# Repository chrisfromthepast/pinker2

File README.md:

# pinker2
 Phantom Powered Pink noise generator

Plug it into a +48V Phantom Powered mic preamp to create pink noise.

Thia project is still in development, and owes EVERYTHING to this thread:
https://groupdiy.com/threads/will-this-48-v-pink-noise-source-work.85625/page-4#post-1117816

A reverse biased BJT provides noise, a op amp gain stage comes next, followed by an op amp filter stage, which does its best to turn white noise into pink noise. the output is impedance balanced.

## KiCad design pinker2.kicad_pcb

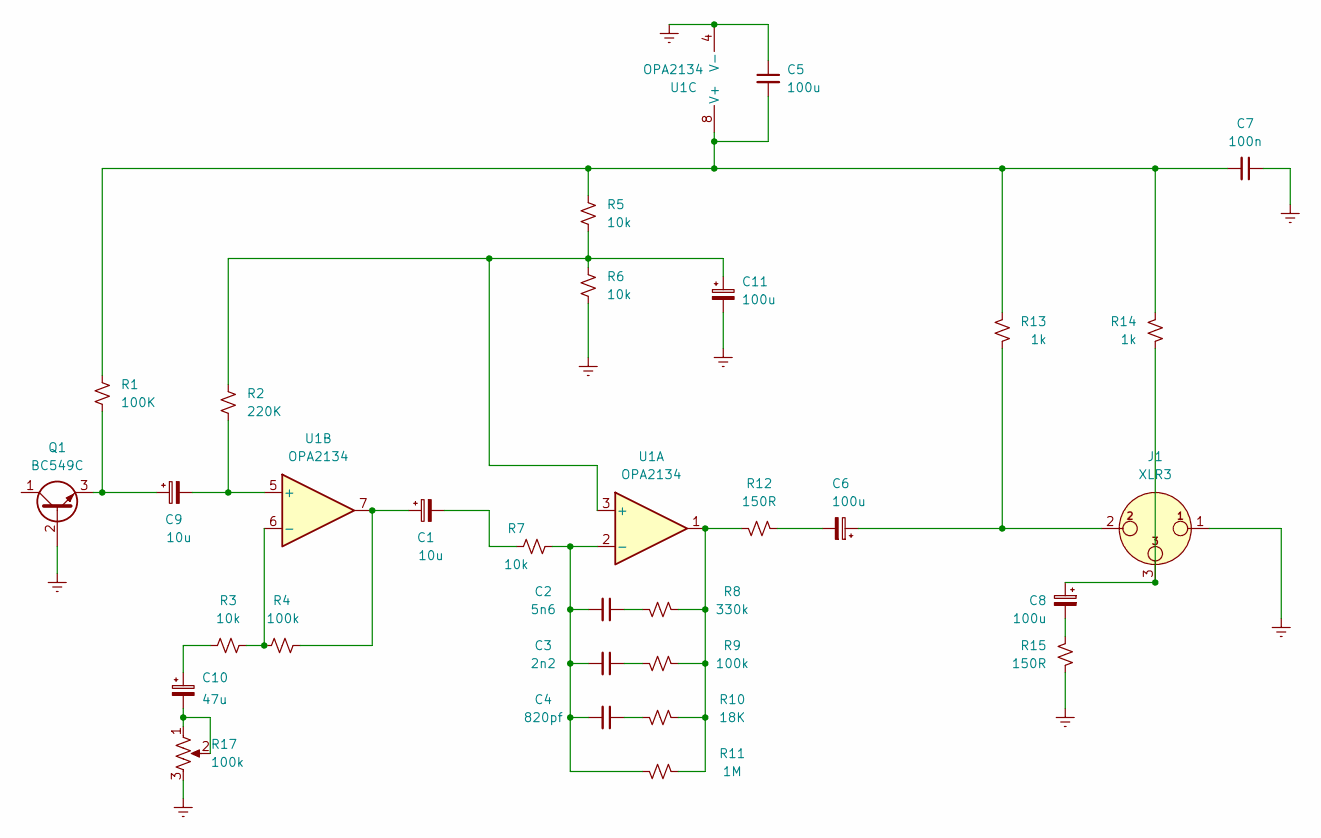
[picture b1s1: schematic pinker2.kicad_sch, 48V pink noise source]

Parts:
C1, C9: 10u; CP_Radial_D4.0mm_P1.50mm
C2: 5n6; C_Disc_D3.0mm_W1.6mm_P2.50mm
C3: 2n2; C_Disc_D3.0mm_W1.6mm_P2.50mm
C4: 820pf; C_Disc_D3.0mm_W1.6mm_P2.50mm
C5, C6, C8, C11: 100u; CP_Radial_D10.0mm_P5.00mm
C7: 100n; C_Disc_D3.0mm_W1.6mm_P2.50mm
C10: 47u; CP_Radial_D4.0mm_P1.50mm
J1: XLR3; Jack_XLR_Neutrik_NC3MBH_Horizontal
Q1: BC549C; TO-92_Inline
R1: 100K; R_Axial_DIN0204_L3.6mm_D1.6mm_P1.90mm_Vertical
R2: 220K; R_Axial_DIN0204_L3.6mm_D1.6mm_P1.90mm_Vertical
R3, R5, R6, R7: 10k; R_Axial_DIN0204_L3.6mm_D1.6mm_P1.90mm_Vertical
R4, R9: 100k; R_Axial_DIN0204_L3.6mm_D1.6mm_P1.90mm_Vertical
R8: 330k; R_Axial_DIN0204_L3.6mm_D1.6mm_P1.90mm_Vertical
R10: 18K; R_Axial_DIN0204_L3.6mm_D1.6mm_P1.90mm_Vertical
R11: 1M; R_Axial_DIN0204_L3.6mm_D1.6mm_P1.90mm_Vertical
R12, R15: 150R; R_Axial_DIN0204_L3.6mm_D1.6mm_P1.90mm_Vertical
R13, R14: 1k; R_Axial_DIN0204_L3.6mm_D1.6mm_P1.90mm_Vertical
R17: 100k; Potentiometer_Bourns_3266X_Horizontal
U1: OPA2134; DIP-8_W7.62mm_Socket

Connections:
Earth: C5.1, C7.1, C11.2, J1.1, Q1.2 (B), R6.1, R15.1, R17.3, U1.4 (V-)
unnamed: C1.1, R4.2, U1.7
unnamed: C1.2, R7.2
unnamed: C2.1, R8.1
unnamed: C2.2, C3.2, C4.2, R7.1, R11.1, U1.2 (-)
unnamed: C3.1, R9.1
unnamed: C4.1, R10.1
unnamed: C5.2, C7.2, R1.2, R5.2, R13.1, R14.1, U1.8 (V+)
unnamed: C6.1, J1.2, R13.2
unnamed: C6.2, R12.2
unnamed: C8.1, J1.3, R14.2
unnamed: C8.2, R15.2
unnamed: C9.1, Q1.3 (E), R1.1
unnamed: C9.2, R2.1, U1.5 (+)
unnamed: C10.1, R3.1
unnamed: C10.2, R17.1, R17.2
unnamed: C11.1, R2.2, R5.1, R6.2, U1.3 (+)
unnamed: R3.2, R4.1, U1.6 (-)
unnamed: R8.2, R9.2, R10.2, R11.2, R12.1, U1.1

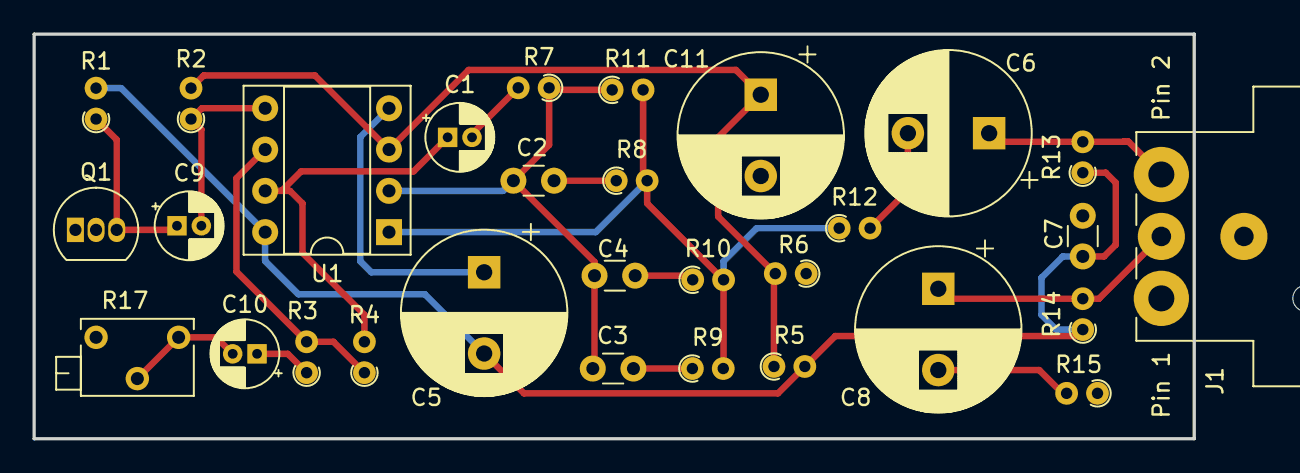
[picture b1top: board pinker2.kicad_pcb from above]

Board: 2 copper layers, 71.4 x 24.9 mm, 30 parts (0 on the bottom side), 19 nets.

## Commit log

2023-11-18 Made Repository
    After the schematic is pretty much final
2023-11-25 layout progress
    started adding traces
2023-11-25 revised to all THT
    changed the pot and the Op amp footprints to through hole
2023-11-25 Delete pinker2.jpg
    file renamed 3d view
2023-11-26 almost complete
    nudged some items, added a ground pour, linked the footprints to a local library (hopefully symbols live there too) added a pdf of the layout to help with visual diffs
2023-11-26 mostly complete
    added some silkscreen notes, and deleted some junk files
